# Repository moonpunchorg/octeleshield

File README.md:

# Overclocking telemetry shield for Arduino Yún

Shield for overclocking telemetry, including:

* multi-channel thermocouple measurement
* multi-channel voltrage measurement

## License

Released under [CERN Open Hardware License 1.2](http://www.ohwr.org/projects/cernohl/wiki).

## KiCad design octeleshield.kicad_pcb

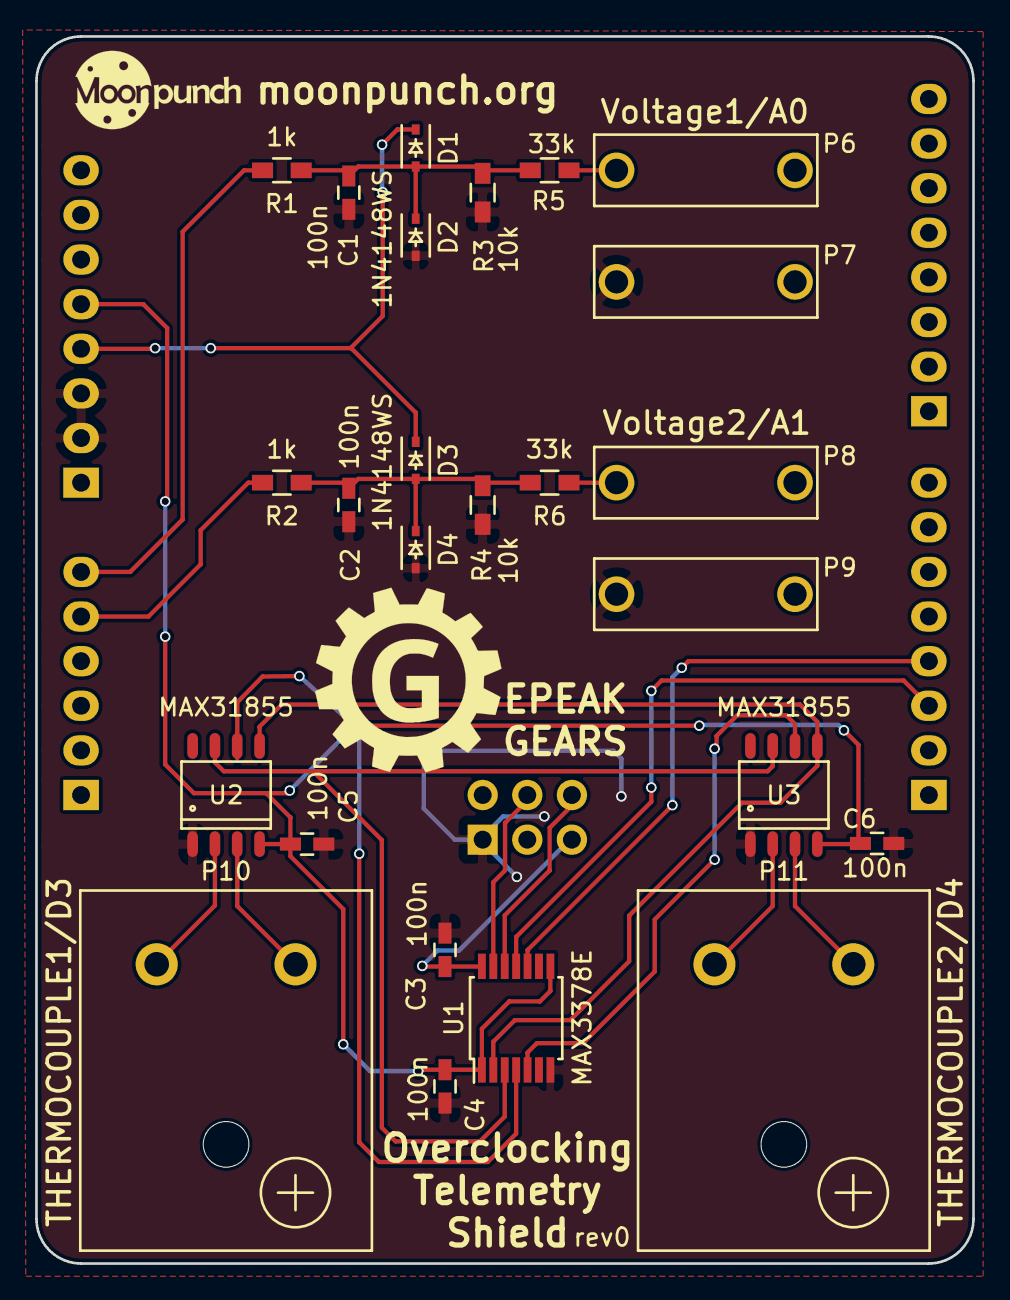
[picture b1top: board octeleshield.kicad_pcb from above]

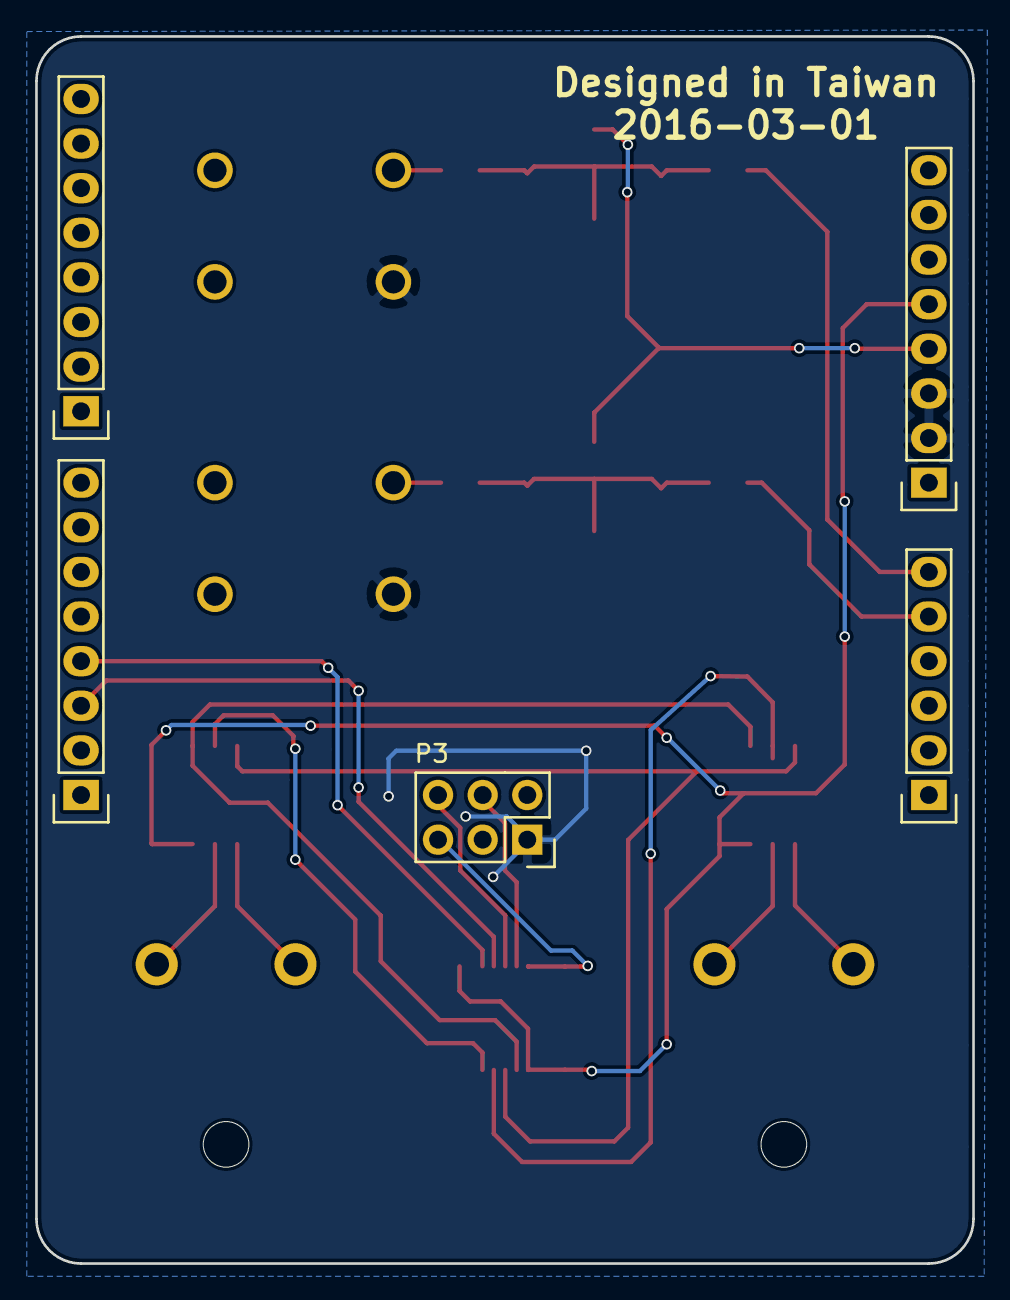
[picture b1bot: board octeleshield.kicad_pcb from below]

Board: 2 copper layers, 53.3 x 69.9 mm, 30 parts (5 on the bottom side), 21 nets.

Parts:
C1, C2, C3, C4, C5, C6: 100n; C_0603_HandSoldering
D1, D2, D3, D4: 1N4148WS; SOD-323
P1: POWER_HEADER; Pin_Header_Straight_1x08
P2: ANALOG_HEADER; Pin_Header_Straight_1x06
P3: ICSP_HEADER; Socket_Strip_Straight_2x03
P4: DIGITAL_HEADER_2; Pin_Header_Straight_1x08
P5: DIGITAL_HEADER_1; Pin_Header_Straight_1x08
P6: V_PROBE1_SIG; Test_Probe
P7: V_PROBE1_GND; Test_Probe
P8: V_PROBE2_SIG; Test_Probe
P9: V_PROBE2_GND; Test_Probe
P10: THERMOCOUPLE1/D3; Thermocouple
P11: THERMOCOUPLE2/D4; Thermocouple
R1, R2: 1k; R_0603_HandSoldering
R3, R4: 10k; R_0603_HandSoldering
R5, R6: 33k; R_0603_HandSoldering
U1: MAX3378E; TSSOP-14_4.4x5mm_Pitch0.65mm
U2, U3: MAX31855; SO-8

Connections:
+3V3: C4.2, C5.2, C6.2, P1.5, U1.1, U1.8, U2.4, U3.4
+5V: C3.1, D1.1, D3.1, P1.4, P3.5, U1.14
/A0: P2.6, R1.2
/A1: P2.5, R2.2
/CS1: P5.3, U1.11
/CS2: P5.4, U1.10
/MISO: P3.6, U1.12
/SCLK: P3.4, U1.13
GND: C1.2, C2.2, C3.2, C4.1, C5.1, C6.1, D2.2, D4.2, P1.2, P1.3, P3.1, P7.1, P9.1, R3.2, R4.2, U1.7, U2.1, U3.1
unnamed: C1.1, D1.2, D2.1, R1.1, R3.1, R5.2
unnamed: C2.1, D3.2, D4.1, R2.1, R4.1, R6.2
unnamed: P6.1, R5.1
unnamed: P8.1, R6.1
unnamed: P10.1, U2.3
unnamed: P10.2, U2.2
unnamed: P11.1, U3.3
unnamed: P11.2, U3.2
unnamed: U1.2, U2.5, U3.5
unnamed: U1.3, U2.7, U3.7
unnamed: U1.4, U2.6
unnamed: U1.5, U3.6

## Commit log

2016-01-10 work in progress
2016-01-10 add .gitignore
2016-01-10 add README
2016-01-11 more work in progress
2016-01-17 work in progress, first try of pcb layout
2016-01-17 some markup and gerber output directory
2016-02-22 work in progress, component updates
2016-02-24 more work in progress, getting there
2016-03-02 PCB modifications
2016-03-02 add gerbers
2016-03-02 update PCB date
2016-03-02 add PDF schematics
2016-03-02 kicad-updated project file

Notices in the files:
octeleshield.kicad_pcb:
CERN OHL 1.2
